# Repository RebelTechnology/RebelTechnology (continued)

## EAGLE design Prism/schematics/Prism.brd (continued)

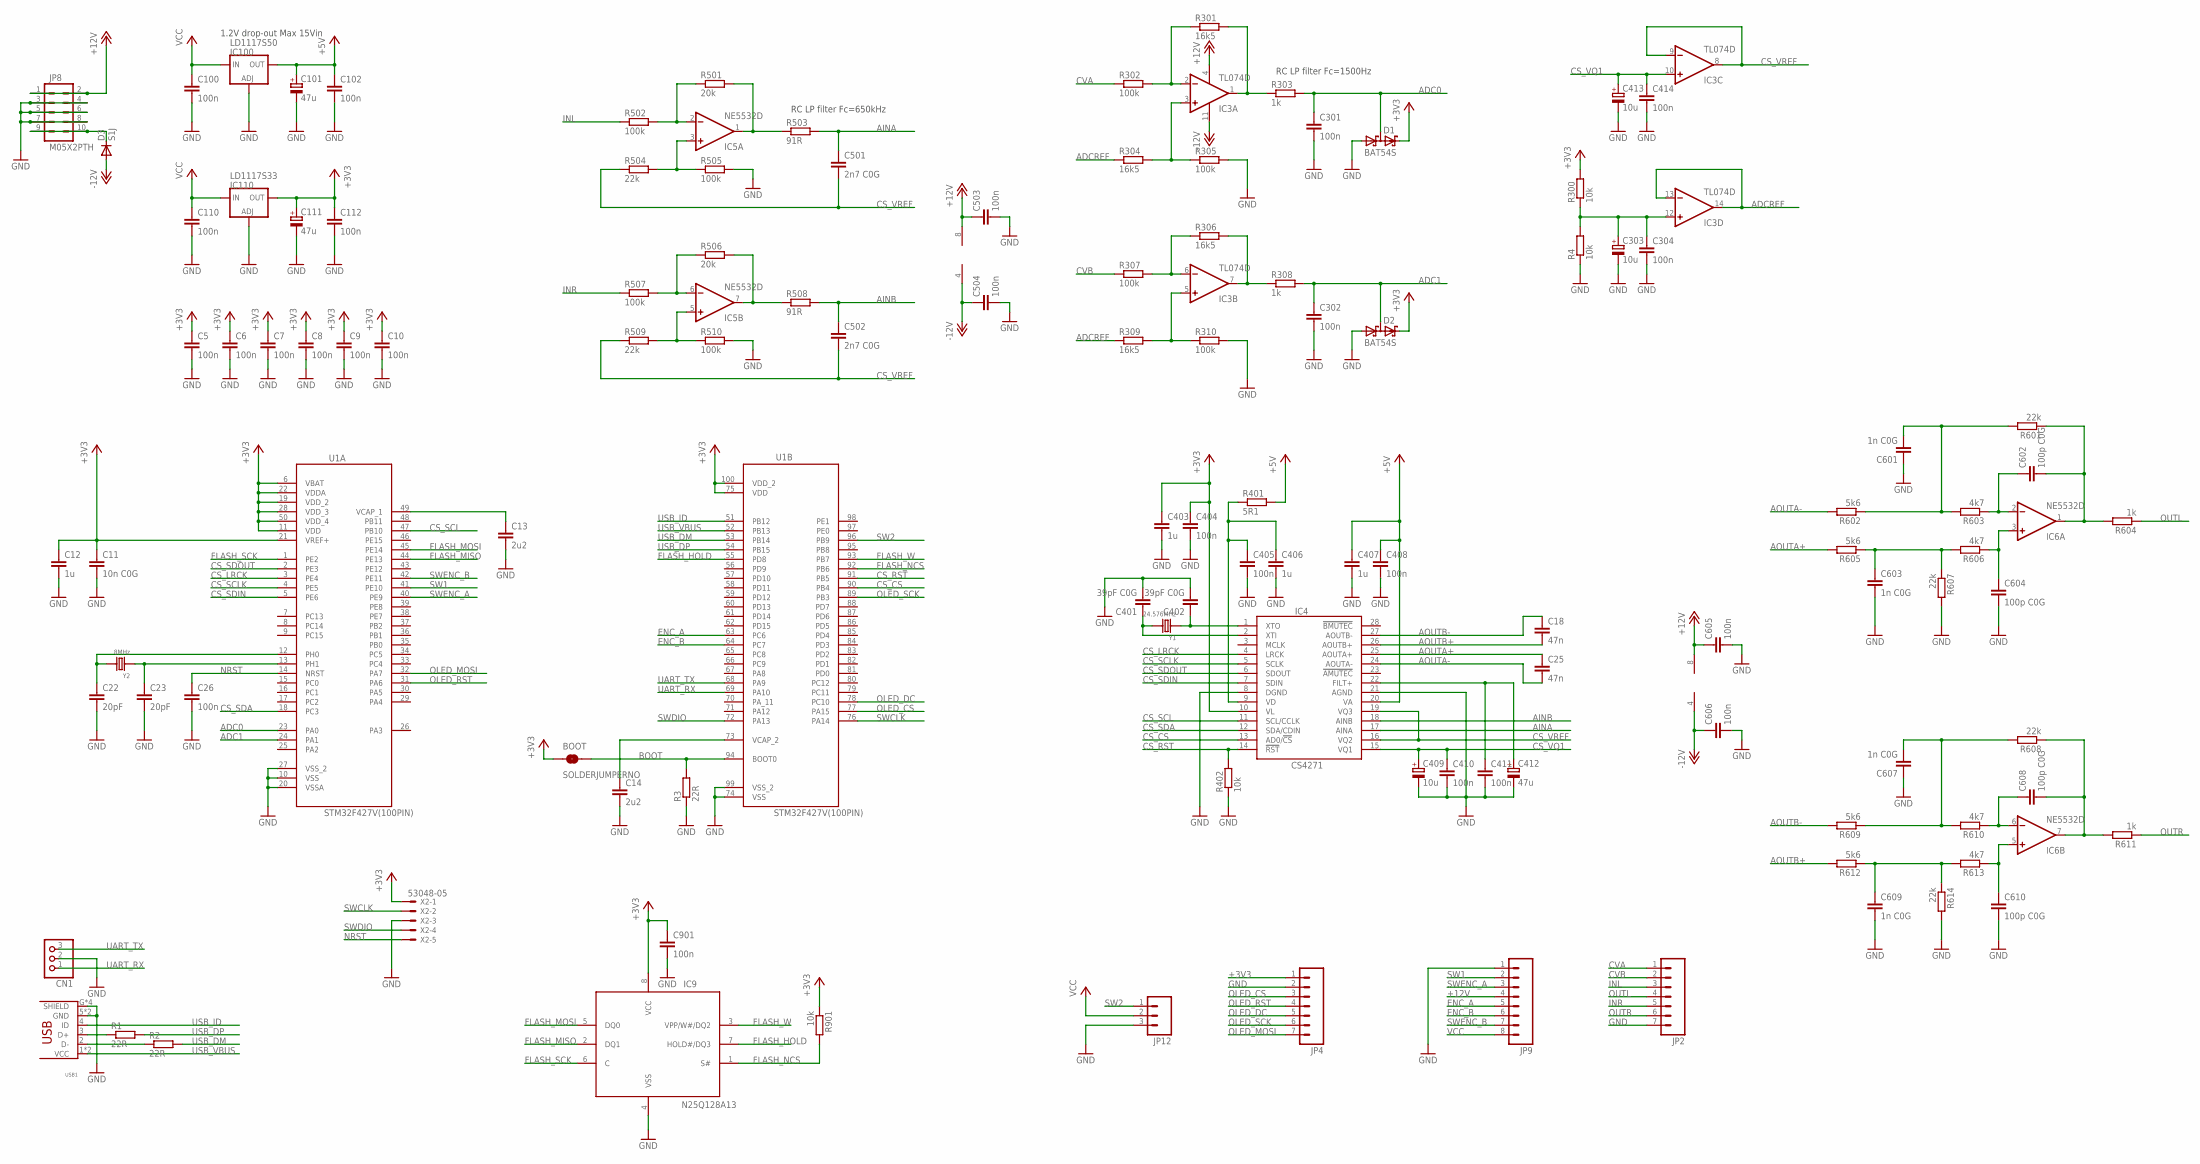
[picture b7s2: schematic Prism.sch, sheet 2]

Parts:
BOOT: SOLDERJUMPERNO; SJ_2S-NO
C5, C6, C7, C8, C9, C10, C26, C100, C102, C110, C112, C301, C302, C304, C404, C405, C408, C410, C411, C414, C503, C504, C605, C606, C901: 100n; C0603
C11: 10n C0G; C0603
C12, C403, C406, C407: 1u; C0603
C13, C14: 2u2; C0603
C18, C25: 47n; C0603
C22, C23: 20pF; C0603
C101, C111, C412: 47u; CPOL-5
C303, C409, C413: 10u; CPOL-5
C401, C402: 39pF C0G; C0603
C501, C502: 2n7 C0G; C0603
C601, C603, C607, C609: 1n C0G; C0603
C602, C604, C608, C610: 100p C0G; C0603
CN1: CON-JST-1X03PH-TH; JST-B3B-PH-KL
D1, D2: BAT54S; SOT23
D3: S1J; SMA-DIODE
IC3: TL074D; SO14
IC4: CS4271; TSSOP28-0.65-9.7X4.4MM
IC5, IC6: NE5532D; SO08
IC9: N25Q128A13; SO8W
IC100: LD1117S50; SOT223
IC110: LD1117S33; SOT223
JP2, JP4: M07; 1X07
JP8: M05X2PTH; AVR_ICSP
JP9: M081X08; 1X08
JP12: M03PTH; 1X03
R1, R2, R3: 22R; 0603
R4, R300, R402, R901: 10k; 0603
R301, R304, R306, R309: 16k5; 0603
R302, R305, R307, R310, R502, R505, R507, R510: 100k; 0603
R303, R308, R604, R611: 1k; 0603
R401: 5R1; 0603
R501, R506: 20k; 0603
R503, R508: 91R; 0603
R504, R509, R601, R607, R608, R614: 22k; 0603
R602, R605, R609, R612: 5k6; 0603
R603, R606, R610, R613: 4k7; 0603
U1: STM32F427V(100PIN); QFP50P1600X1600X160-100N
USB1: USB_HRS_ZX62-B-5PA(11)MICRO.B-; HRS_ZX62D-AB-5P8_USB
X2: 53048-05
Y1: 24.576MHz; X2-SMD-5.0X3.2X1.3MM
Y2: 8MHz; X2-SMD-5.0X3.2X1.3MM

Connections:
+3V3: BOOT.1, C5.1, C6.1, C7.1, C8.1, C9.1, C10.1, C11.1, C12.1, C111.+, C112.1, C403.1, C404.1, C901.1, D1.2 (C2), D2.2 (C2), IC4.10 (VL), IC9.8 (VCC), IC110.2 (OUT), IC110.4 (OUT), JP4.1, R300.2, R901.1, U1.6 (VBAT), U1.11 (VDD), U1.19 (VDD_2), U1.21 (VREF+), U1.22 (VDDA), U1.28 (VDD_3), U1.50 (VDD_4), U1.75 (VDD), U1.100 (VDD_2), X2.1
+5V: C101.+, C102.1, C407.1, C408.1, IC4.20 (VA), IC100.2 (OUT), IC100.4 (OUT), R401.2
+12V: C503.1, C605.1, IC3.4 (V+), IC5.8 (V+), IC6.8 (V+), JP8.1, JP8.2, JP9.4
-12V: C504.1, C606.1, D3.A, IC3.11 (V-), IC5.4 (V-), IC6.4 (V-)
ADC0: C301.1, D1.3 (C1A2), R303.2, U1.23 (PA0)
ADC1: C302.1, D2.3 (C1A2), R308.2, U1.24 (PA1)
ADCREF: IC3.13 (-IN), IC3.14 (OUT), R304.1, R309.1
AINA: C501.1, IC4.17 (AINA), R503.2
AINB: C502.1, IC4.18 (AINB), R508.2
ANALOG_OUTA: C602.2, IC6.1 (OUT), R601.1, R604.2
ANALOG_OUTB: C608.2, IC6.7 (OUT), R608.1, R611.2
AOUTA+: C25.1, IC4.25 (AOUTA+), R605.2
AOUTA-: C25.2, IC4.24 (AOUTA-), R602.2
AOUTB+: C18.2, IC4.26 (AOUTB+), R612.2
AOUTB-: C18.1, IC4.27 (AOUTB-), R609.2
BOOT: BOOT.2, R3.2, U1.94 (BOOT0)
CS_CS: IC4.13 (AD0/!CS), U1.90 (PB4)
CS_LRCK: IC4.4 (LRCK), U1.3 (PE4)
CS_RST: IC4.14 (!RST), R402.2, U1.91 (PB5)
CS_SCL: IC4.11 (SCL/CCLK), U1.47 (PB10)
CS_SCLK: IC4.5 (SCLK), U1.4 (PE5)
CS_SDA: IC4.12 (SDA/CDIN), U1.18 (PC3)
CS_SDIN: IC4.7 (SDIN), U1.5 (PE6)
CS_SDOUT: IC4.6 (SDOUT), U1.2 (PE3)
CS_VQ1: C409.+, C410.1, C413.+, C414.1, IC3.10 (+IN), IC4.15 (VQ1)
CS_VREF: C501.2, C502.2, IC3.8 (OUT), IC3.9 (-IN), IC4.16 (VQ2), IC4.19 (VQ3), R504.1, R509.1
CVA: JP2.1, R302.1
CVB: JP2.2, R307.1
ENC_A: JP9.5, U1.63 (PC6)
ENC_B: JP9.6, U1.64 (PC7)
FLASH_HOLD: IC9.7 (HOLD#/DQ3), U1.55 (PD8)
FLASH_MISO: IC9.2 (DQ1), U1.44 (PE13)
FLASH_MOSI: IC9.5 (DQ0), U1.45 (PE14)
FLASH_NCS: IC9.1 (S#), R901.2, U1.92 (PB6)
FLASH_SCK: IC9.6 (C), U1.1 (PE2)
FLASH_W: IC9.3 (VPP/W#/DQ2), U1.93 (PB7)
GND: C5.2, C6.2, C7.2, C8.2, C9.2, C10.2, C11.2, C12.2, C13.2, C14.2, C22.2, C23.2, C26.2, C100.2, C101.-, C102.2, C110.2, C111.-, C112.2, C301.2, C302.2, C303.-, C304.2, C401.2, C402.2, C403.2, C404.2, C405.2, C406.2, C407.2, C408.2, C409.-, C410.2, C411.2, C412.-, C413.-, C414.2, C503.2, C504.2, C601.1, C603.2, C604.2, C605.2, C606.2, C607.1, C609.2, C610.2, C901.2, CN1.2, D1.1 (A1), D2.1 (A1), IC4.8 (DGND), IC4.21 (AGND), IC9.4 (VSS), IC100.1 (ADJ), IC110.1 (ADJ), JP2.7, JP4.2, JP8.3, JP8.4, JP8.5, JP8.6, JP8.7, JP8.8, JP9.1, JP12.3, R3.1, R4.1, R305.2, R310.2, R402.1, R505.2, R510.2, R607.2, R614.2, U1.10 (VSS), U1.20 (VSSA), U1.27 (VSS_2), U1.74 (VSS), U1.99 (VSS_2), USB1.5 (GND), USB1.7 (GND), USB1.G (SHIELD), USB1.G2 (SHIELD), USB1.G3 (SHIELD), USB1.G4 (SHIELD), X2.3
INL: JP2.3, R502.1
INR: JP2.5, R507.1
unnamed: C603.1, R605.1, R606.2, R607.1
unnamed: IC3.3 (+IN), R304.2, R305.1
unnamed: IC3.2 (-IN), R301.1, R302.2
unnamed: IC3.1 (OUT), R301.2, R303.1
unnamed: D3.C, JP8.9, JP8.10
unnamed: C601.2, R601.2, R602.1, R603.2
unnamed: C13.1, U1.49 (VCAP_1)
unnamed: C23.1, U1.13 (PH1), Y2.1
unnamed: C602.1, IC6.2 (-IN), R603.1
unnamed: C604.1, IC6.3 (+IN), R606.1
unnamed: C22.1, U1.12 (PH0), Y2.2
unnamed: C14.1, U1.73 (VCAP_2)
unnamed: C402.1, IC4.1 (XTO), Y1.1
unnamed: R1.1, USB1.3 (D+)
unnamed: C411.1, C412.+, IC4.22 (FILT+)
unnamed: C401.1, IC4.2 (XTI), Y1.2
unnamed: R2.1, USB1.2 (D-)
unnamed: C609.1, R612.1, R613.2, R614.1
unnamed: C607.2, R608.2, R609.1, R610.2
unnamed: C608.1, IC6.6 (-IN), R610.1
unnamed: C610.1, IC6.5 (+IN), R613.1
unnamed: IC5.3 (+IN), R504.2, R505.1
unnamed: IC5.2 (-IN), R501.1, R502.2
unnamed: IC5.1 (OUT), R501.2, R503.1
unnamed: IC5.5 (+IN), R509.2, R510.1
unnamed: IC5.6 (-IN), R506.1, R507.2
unnamed: IC5.7 (OUT), R506.2, R508.1
unnamed: C303.+, C304.1, IC3.12 (+IN), R4.2, R300.1
unnamed: IC3.5 (+IN), R309.2, R310.1
unnamed: IC3.6 (-IN), R306.1, R307.2
unnamed: IC3.7 (OUT), R306.2, R308.1
NRST: C26.1, U1.14 (NRST), X2.5
OLED_CS: JP4.3, U1.77 (PA15)
OLED_DC: JP4.5, U1.78 (PC10)
OLED_MOSI: JP4.7, U1.32 (PA7)
OLED_RST: JP4.4, U1.31 (PA6)
OLED_SCK: JP4.6, U1.89 (PB3)
OUTL: JP2.4, R604.1
OUTR: JP2.6, R611.1
SW1: JP9.2, U1.41 (PE10)
SW2: JP12.1, U1.96 (PB9)
SWCLK: U1.76 (PA14), X2.2
SWDIO: U1.72 (PA13), X2.4
SWENC_A: JP9.3, U1.40 (PE9)
SWENC_B: JP9.7, U1.42 (PE11)
UART_RX: CN1.1, U1.69 (PA10)
UART_TX: CN1.3, U1.68 (PA9)
USB_DM: R2.2, U1.53 (PB14)
USB_DP: R1.2, U1.54 (PB15)
USB_ID: U1.51 (PB12), USB1.4 (ID)
USB_VBUS: U1.52 (PB13), USB1.1 (VCC), USB1.6 (VCC)
VCC: C100.1, C110.1, IC100.3 (IN), IC110.3 (IN), JP9.8, JP12.2
VD: C405.1, C406.1, IC4.9 (VD), R401.1

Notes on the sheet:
RC LP filter Fc=650kHz
RC LP filter Fc=1500Hz
1.2V drop-out Max 15Vin

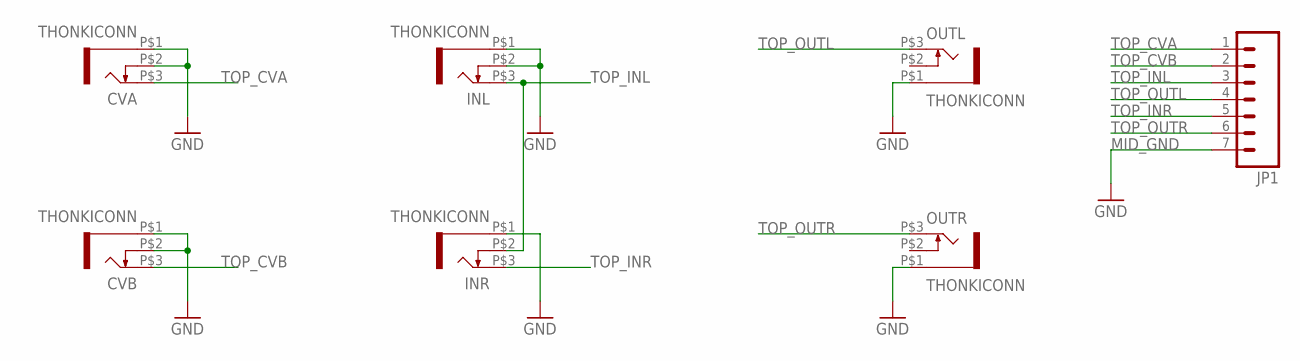
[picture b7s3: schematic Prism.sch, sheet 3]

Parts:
CVA: THONKICONN
CVB: THONKICONN
INL: THONKICONN
INR: THONKICONN
JP1: M07; 1X07
OUTL: THONKICONN
OUTR: THONKICONN

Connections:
MID_GND: CVA.P$1 (5), CVA.P$2 (4), CVB.P$1 (5), CVB.P$2 (4), INL.P$1 (5), INL.P$2 (4), INR.P$1 (5), JP1.7, OUTL.P$1 (5), OUTR.P$1 (5)
TOP_CVA: CVA.P$3 (3), JP1.1
TOP_CVB: CVB.P$3 (3), JP1.2
TOP_INL: INL.P$3 (3), INR.P$2 (4), JP1.3
TOP_INR: INR.P$3 (3), JP1.5
TOP_OUTL: JP1.4, OUTL.P$3 (3)
TOP_OUTR: JP1.6, OUTR.P$3 (3)

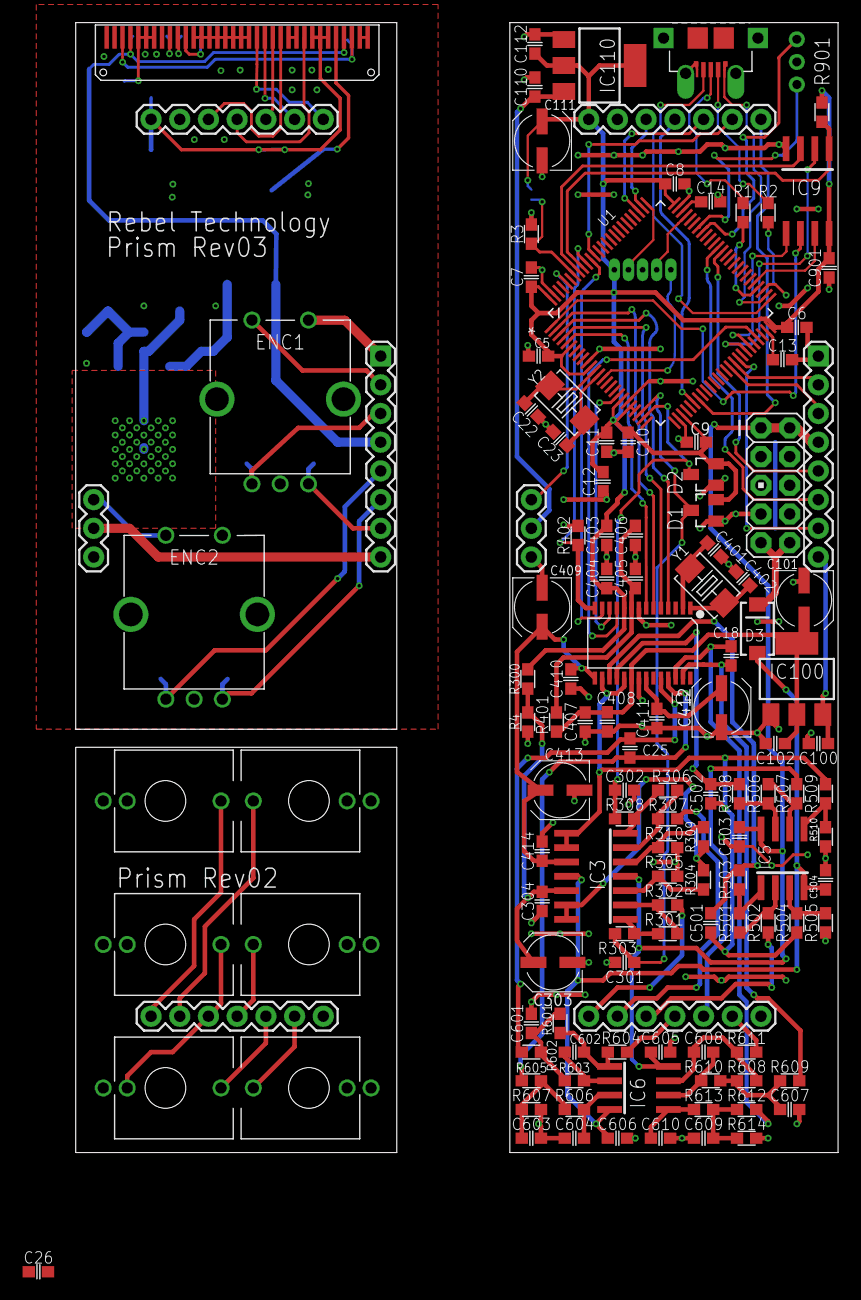
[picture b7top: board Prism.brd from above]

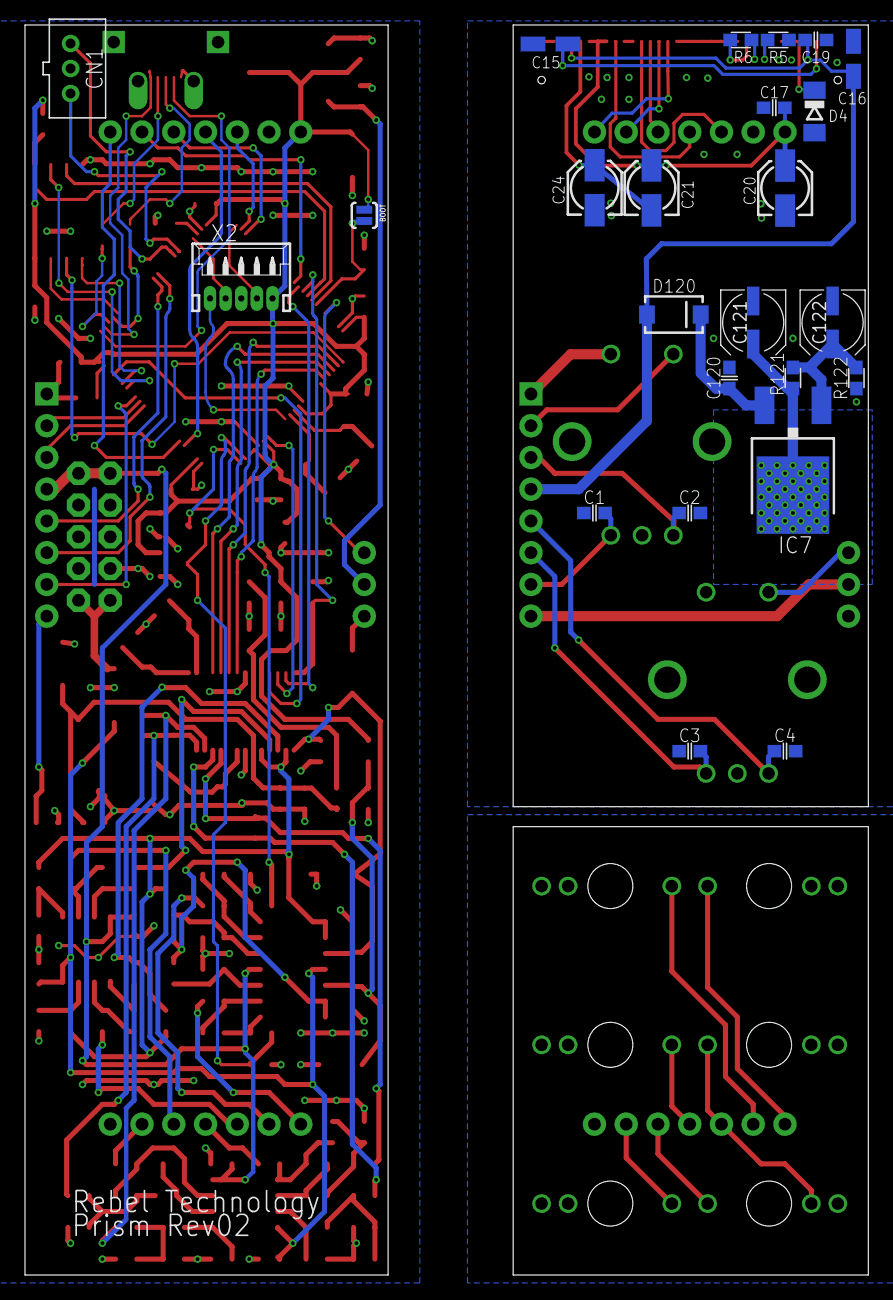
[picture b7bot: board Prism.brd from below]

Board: 2 copper layers, 67.5 x 100.0 mm, 152 parts (24 on the bottom side), 122 nets.
